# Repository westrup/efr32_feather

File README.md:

EFR32 Feather Board
===================

This is an Adafruit Feather compatible PCB with a Silicon Labs EFR32 MCU.
This MCU supports 2.4GHz radio such as BLE, Zigbee, Thread

Hardware components:
* MCU: EFR32 with 1024kB FLASH, 256kB RAM EFR32MG12P332F1024GM48
* USB Serial interface: CP2102N
* 3.3V LDO: AP2112K
* Charging: MCP73832

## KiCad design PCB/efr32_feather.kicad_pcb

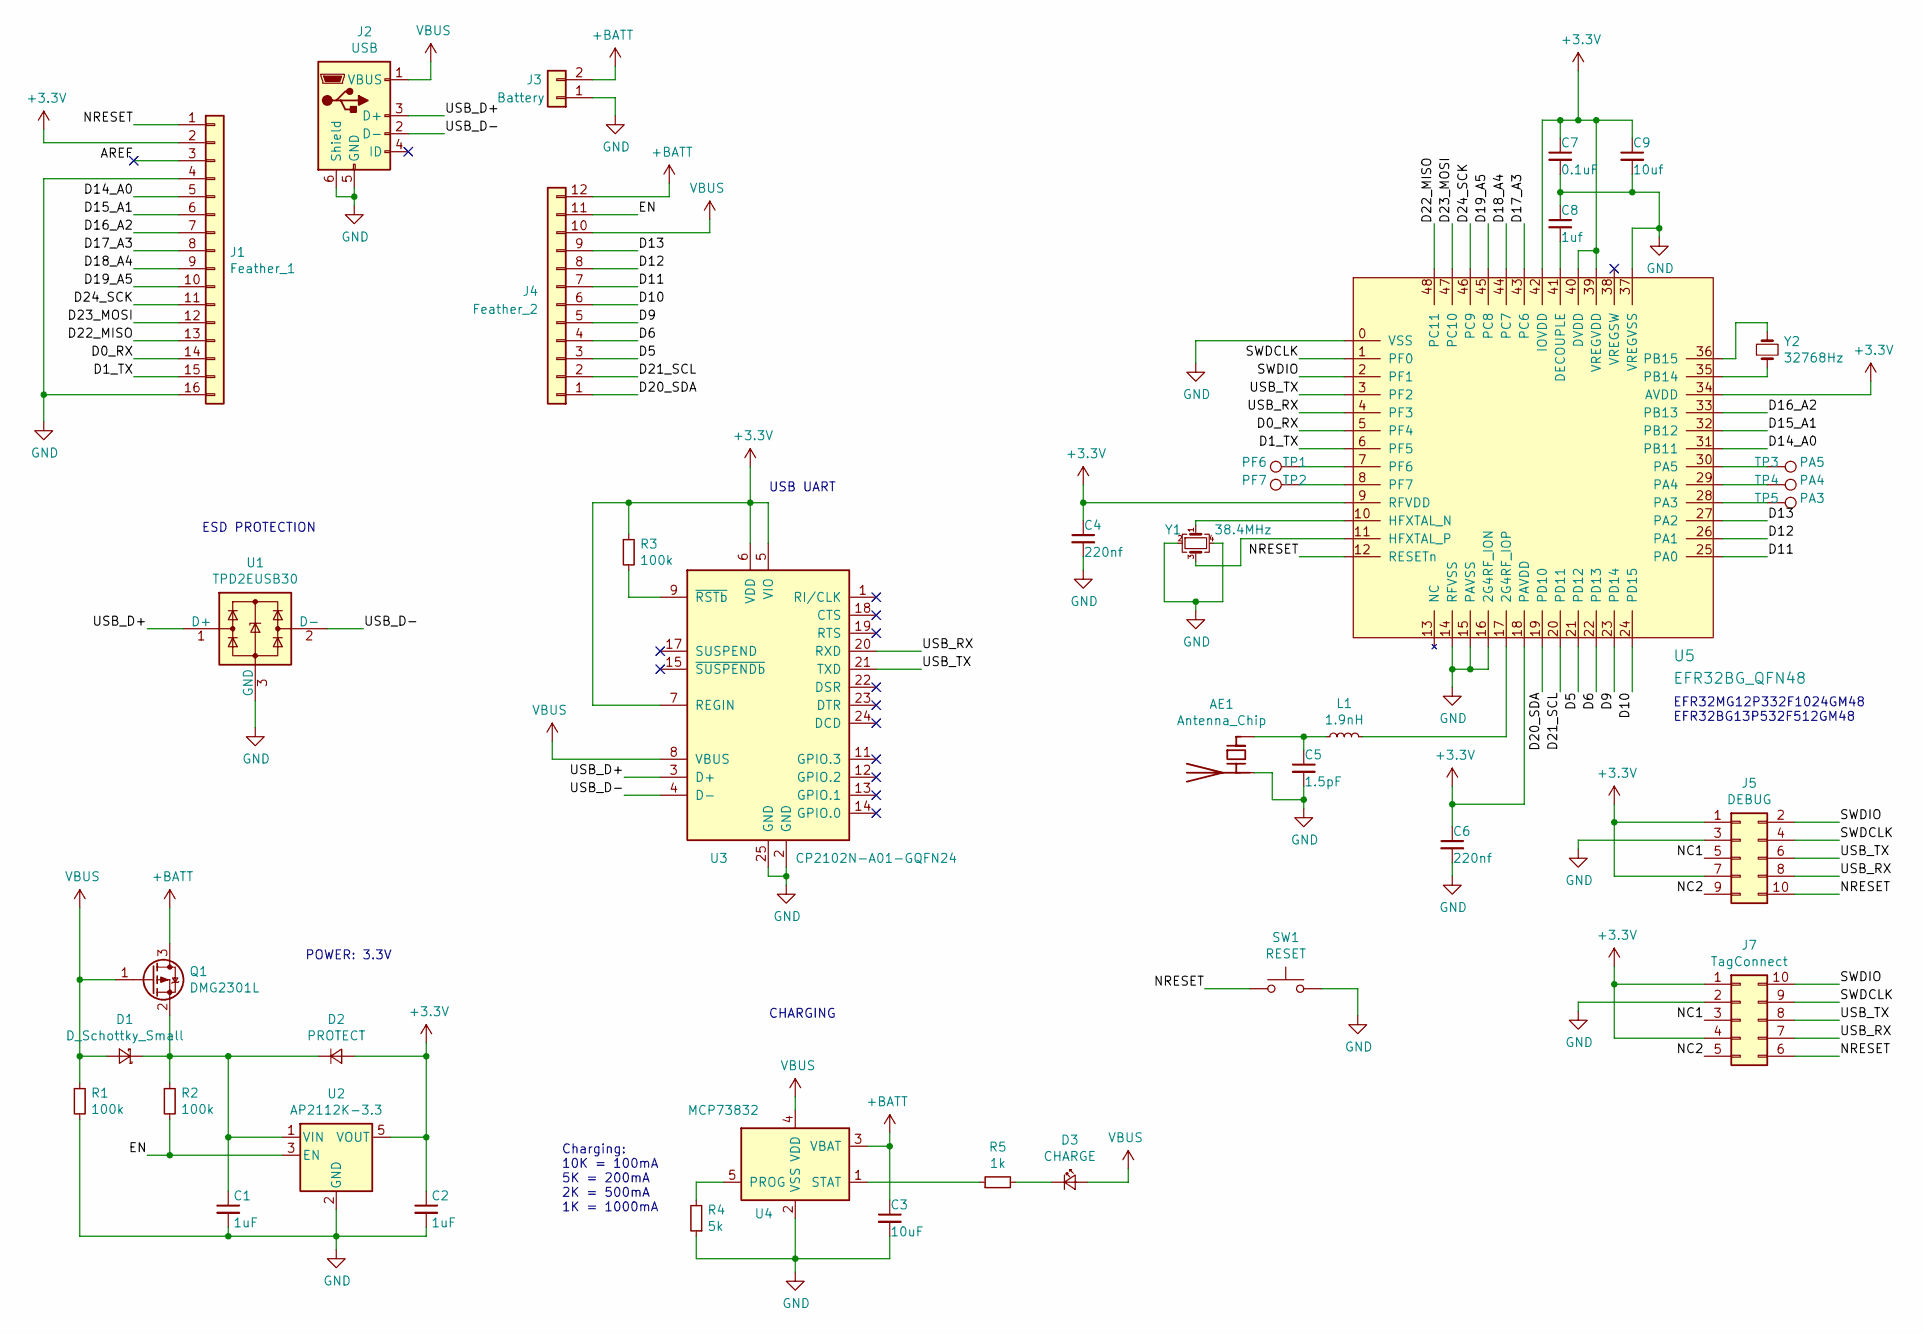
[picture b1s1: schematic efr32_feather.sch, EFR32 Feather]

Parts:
AE1: Antenna_Chip; Texas_SWRA117D_2.4GHz_Right
C1, C2: 1uF; C_0603_1608Metric
C3: 10uF; C_0603_1608Metric
C4, C6: 220nf; C_0603_1608Metric
C5: 1.5pF; C_0402_1005Metric
C7: 0.1uF; C_0603_1608Metric
C8: 1uf; C_0603_1608Metric
C9: 10uf; C_0603_1608Metric
D1: D_Schottky_Small; D_SOD-323
D2: PROTECT; D_SOD-323
D3: CHARGE; LED_0603_1608Metric
J1: Feather_1; PinHeader_1x16_P2.54mm_Vertical
J2: USB; USB_Micro-B_Molex-105017-0001
J3: Battery; JST_PH_S2B-PH-K_1x02_P2.00mm_Horizontal
J4: Feather_2; PinHeader_1x12_P2.54mm_Vertical
J5: DEBUG; PinHeader_2x05_P1.27mm_Vertical_SMD
J7: TagConnect; Tag-Connect_TC2050-IDC-NL_2x05_P1.27mm_Vertical
L1: 1.9nH; L_0402_1005Metric
Q1: DMG2301L; SOT-23
R1, R2, R3: 100k; R_0603_1608Metric
R4: 5k; R_0603_1608Metric
R5: 1k; R_0603_1608Metric
SW1: RESET; SW_SPST_B3U-1000P
TP1: PF6; TestPoint_Pad_D1.0mm
TP2: PF7; TestPoint_Pad_D1.0mm
TP3: PA5; TestPoint_Pad_D1.0mm
TP4: PA4; TestPoint_Pad_D1.0mm
TP5: PA3; TestPoint_Pad_D1.0mm
U1: TPD2EUSB30; Texas_DRT-3
U2: AP2112K-3.3; SOT-23-5
U3: CP2102N-A01-GQFN24; QFN-24-1EP_4x4mm_P0.5mm_EP2.6x2.6mm
U4: MCP73832; SOT-23-5
U5: EFR32BG_QFN48; QFN-48-1_PIN0_EP_7x7mm_P0.5mm_EP5.3x5.3mm
Y1: 38.4MHz; Crystal_SMD_3225-4Pin_3.2x2.5mm
Y2: 32768Hz; Crystal_SMD_3215-2Pin_3.2x1.5mm

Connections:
+3V3: C2.1, C4.1, C6.1, C7.1, C9.1, D2.2 (A), J1.2, J5.1, J5.7, J7.1, J7.4, R3.1, U2.5 (VOUT), U3.5 (VIO), U3.6 (VDD), U3.7 (REGIN), U5.9 (RFVDD), U5.18 (PAVDD), U5.34 (AVDD), U5.39 (VREGVDD), U5.40 (DVDD), U5.42 (IOVDD)
+BATT: C3.1, J3.2, J4.12, Q1.3 (D), U4.3 (VBAT)
/AREF: J1.3
/D0_RX: J1.14, U5.5 (PF4)
/D1_TX: J1.15, U5.6 (PF5)
/D5: J4.3, U5.21 (PD12)
/D6: J4.4, U5.22 (PD13)
/D9: J4.5, U5.23 (PD14)
/D10: J4.6, U5.24 (PD15)
/D11: J4.7, U5.25 (PA0)
/D12: J4.8, U5.26 (PA1)
/D13: J4.9, U5.27 (PA2)
/D14_A0: J1.5, U5.31 (PB11)
/D15_A1: J1.6, U5.32 (PB12)
/D16_A2: J1.7, U5.33 (PB13)
/D17_A3: J1.8, U5.43 (PC6)
/D18_A4: J1.9, U5.44 (PC7)
/D19_A5: J1.10, U5.45 (PC8)
/D20_SDA: J4.1, U5.19 (PD10)
/D21_SCL: J4.2, U5.20 (PD11)
/D22_MISO: J1.13, U5.48 (PC11)
/D23_MOSI: J1.12, U5.47 (PC10)
/D24_SCK: J1.11, U5.46 (PC9)
/EN: J4.11, R2.2, U2.3 (EN)
/NC1: J5.5, J7.3
/NC2: J5.9, J7.5
/NRESET: J1.1, J5.10, J7.6, SW1.1, U5.12 (RESETn)
/SWDCLK: J5.4, J7.9, U5.1 (PF0)
/SWDIO: J5.2, J7.10, U5.2 (PF1)
/USB_D+: J2.3 (D+), U1.1 (D+), U3.3 (D+)
/USB_D-: J2.2 (D-), U1.2 (D-), U3.4 (D-)
/USB_RX: J5.8, J7.7, U3.20 (RXD), U5.4 (PF3)
/USB_TX: J5.6, J7.8, U3.21 (TXD), U5.3 (PF2)
GND: AE1.2 (PCB_Trace), C1.2, C2.2, C3.2, C4.2, C5.2, C6.2, C7.2, C8.1, C9.2, J1.4, J1.16, J2.5 (GND), J2.6 (Shield), J3.1, J5.3, J7.2, R1.2, R4.1, SW1.2, U1.3 (GND), U2.2 (GND), U3.2 (GND), U3.25 (GND), U4.2 (VSS), U5.0 (VSS), U5.14 (RFVSS), U5.15 (PAVSS), U5.16 (2G4RF_ION), U5.37 (VREGVSS), Y1.2, Y1.4
unnamed: AE1.1 (FEED), C5.1, L1.1
unnamed: C1.1, D1.1 (K), D2.1 (K), Q1.2 (S), R2.1, U2.1 (VIN)
unnamed: C8.2, U5.41 (DECOUPLE)
unnamed: D3.1 (K), R5.2
unnamed: L1.2, U5.17 (2G4RF_IOP)
unnamed: R3.2, U3.9 (~RSTb)
unnamed: R4.2, U4.5 (PROG)
unnamed: R5.1, U4.1 (STAT)
unnamed: TP1.1, U5.7 (PF6)
unnamed: TP2.1, U5.8 (PF7)
unnamed: TP3.1, U5.30 (PA5)
unnamed: TP4.1, U5.29 (PA4)
unnamed: TP5.1, U5.28 (PA3)
unnamed: U5.10 (HFXTAL_N), Y1.1
unnamed: U5.11 (HFXTAL_P), Y1.3
unnamed: U5.35 (PB14), Y2.2
unnamed: U5.36 (PB15), Y2.1
VBUS: D1.2 (A), D3.2 (A), J2.1 (VBUS), J4.10, Q1.1 (G), R1.1, U3.8 (VBUS), U4.4 (VDD)

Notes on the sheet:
Charging: 10K = 100mA 5K = 200mA 2K = 500mA 1K = 1000mA
CHARGING
POWER: 3.3V
USB UART
ESD PROTECTION
EFR32MG12P332F1024GM48 EFR32BG13P532F512GM48

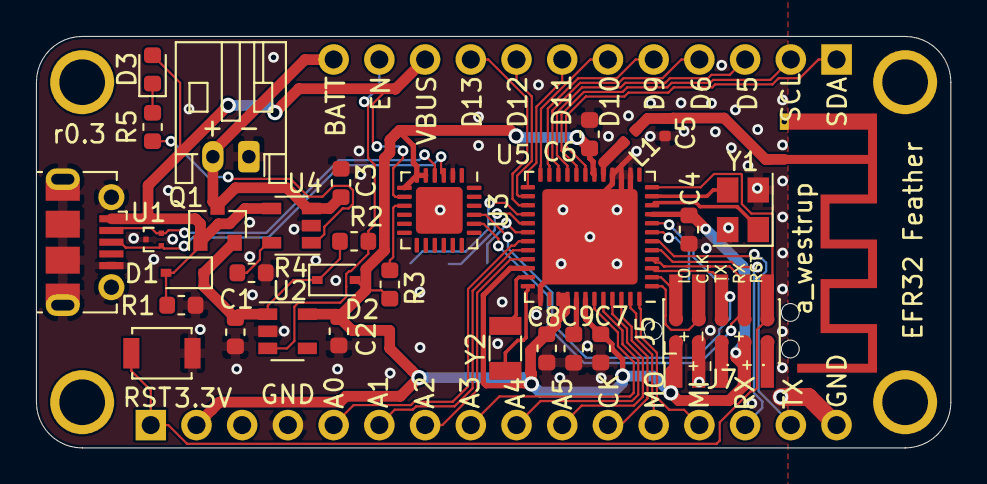
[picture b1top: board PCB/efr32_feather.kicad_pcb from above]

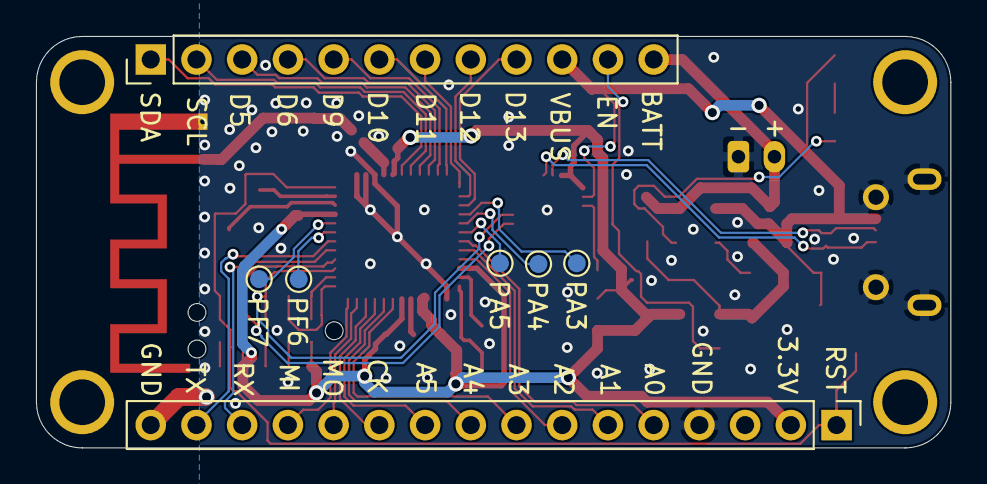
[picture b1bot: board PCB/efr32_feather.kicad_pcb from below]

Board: 2 copper layers, 50.8 x 22.9 mm, 40 parts (7 on the bottom side), 51 nets.

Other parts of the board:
PCB**: VAL**; PCB_FeatherWing

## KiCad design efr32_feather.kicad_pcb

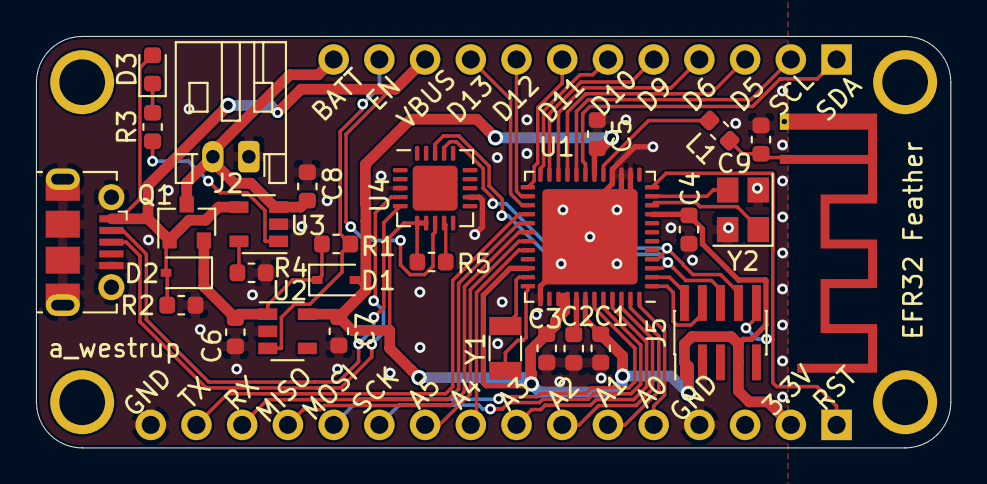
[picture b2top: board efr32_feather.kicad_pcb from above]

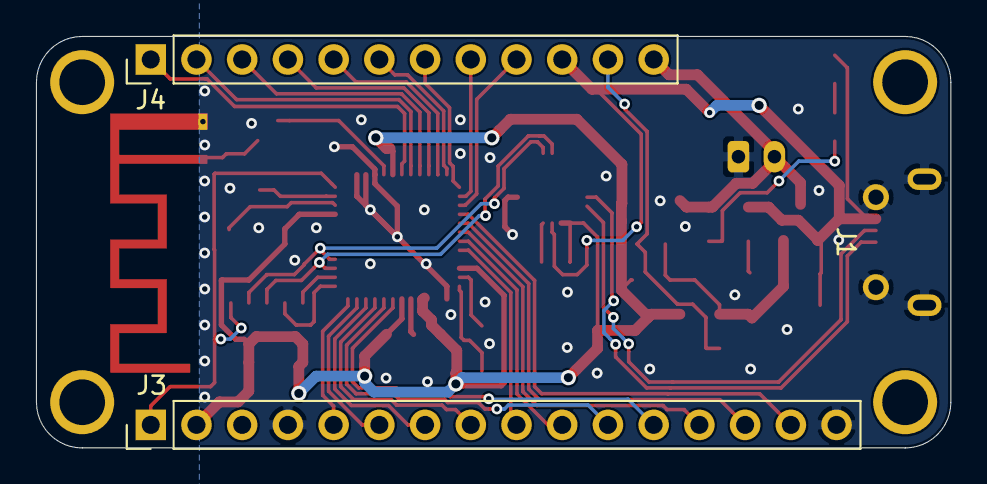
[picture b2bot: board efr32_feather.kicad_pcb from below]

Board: 2 copper layers, 50.8 x 22.9 mm, 32 parts (2 on the bottom side), 44 nets.

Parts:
AE1: Antenna_Chip; Texas_SWRA117D_2.4GHz_Right
C1: 0.1uF; C_0603_1608Metric
C2: 10uf; C_0603_1608Metric
C3: 1uf; C_0603_1608Metric
C4, C5: 220nf; C_0603_1608Metric
C6, C7: 1uF; C_0603_1608Metric
C8: 10uF; C_0603_1608Metric
C9: 1.5pF; C_0603_1608Metric
D1: PROTECT; D_SOD-323
D2: D_Schottky_Small; D_SOD-323
D3: CHARGE; LED_0603_1608Metric
J1: USB; USB_Micro-B_Molex-105017-0001
J2: Battery; JST_PH_S2B-PH-K_1x02_P2.00mm_Horizontal
J3: Feather_1; PinHeader_1x16_P2.54mm_Vertical
J4: Feather_2; PinHeader_1x12_P2.54mm_Vertical
J5: DEBUG; PinHeader_2x05_P1.00mm_Vertical_SMD
L1: 1.9nH; L_0603_1608Metric
PCB**: VAL**; PCB_FeatherWing
Q1: DMG2301L; SOT-23
R1, R2, R5: 100k; R_0603_1608Metric
R3: 1k; R_0603_1608Metric
R4: 5k; R_0603_1608Metric
U1: EFR32BG_QFN48; QFN-48-1_PIN0_EP_7x7mm_P0.5mm_EP5.3x5.3mm
U2: AP2112K-3.3; SOT-23-5
U3: MCP73831-2-OT; SOT-23-5
U4: CP2102N-A01-GQFN20; QFN-20-1EP_4x4mm_P0.5mm_EP2.5x2.5mm
Y1: 32768Hz; Crystal_SMD_3215-2Pin_3.2x1.5mm
Y2: 38.4MHz; Crystal_SMD_3225-4Pin_3.2x2.5mm

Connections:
+3V3: C1.1, C2.1, C4.1, C5.1, C7.1, D1.2, J3.2, J5.1, J5.7, R5.1, U1.9, U1.18, U1.34, U1.39, U1.40, U1.42, U2.5, U4.6, U4.7
+BATT: C8.1, J2.2, J4.12, Q1.3, U3.3
/D0_RX: J3.14, U1.29
/D1_TX: J3.15, U1.28
/D5: J4.3, U1.21
/D6: J4.4, U1.22
/D9: J4.5, U1.23
/D10: J4.6, U1.24
/D11: J4.7, U1.25
/D12: J4.8, U1.26
/D13: J4.9, U1.27
/D14_A0: J3.5, U1.48
/D15_A1: J3.6, U1.47
/D16_A2: J3.7, U1.46
/D17_A3: J3.8, U1.45
/D18_A4: J3.9, U1.32
/D19_A5: J3.10, U1.31
/D20_SDA: J4.1, U1.19
/D21_SCL: J4.2, U1.20
/D22_MISO: J3.13, U1.30
/D23_MOSI: J3.12, U1.43
/D24_SCK: J3.11, U1.44
/EN: J4.11, R1.2, U2.3
/NRESET: J3.1, J5.10, U1.12
/SWDCLK: J5.4, U1.1
/SWDIO: J5.2, U1.2
/USB_D+: J1.3, U4.4
/USB_D-: J1.2, U4.5
/USB_RX: J5.8, U1.4, U4.17
/USB_TX: J5.6, U1.3, U4.18
GND: AE1.2, C1.2, C2.2, C3.1, C4.2, C5.2, C6.2, C7.2, C8.2, C9.2, J1.5, J1.6, J2.1, J3.4, J3.16, J5.3, R2.2, R4.1, U1.0, U1.14, U1.15, U1.16, U1.37, U2.2, U3.2, U4.3, U4.12, Y2.2, Y2.4
unnamed: AE1.1, C9.1, L1.1
unnamed: C3.2, U1.41
unnamed: C6.1, D1.1, D2.1, Q1.2, R1.1, U2.1
unnamed: D3.1, R3.2
unnamed: L1.2, U1.17
unnamed: R3.1, U3.1
unnamed: R4.2, U3.5
unnamed: R5.2, U4.9
unnamed: U1.10, Y2.1
unnamed: U1.11, Y2.3
unnamed: U1.35, Y1.2
unnamed: U1.36, Y1.1
VBUS: D2.2, D3.2, J1.1, J4.10, Q1.1, R2.1, U3.4, U4.8

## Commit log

2019-09-16 EFR32 Feather
2019-09-16 Change debug connector
2019-09-16 Reversed pin header, better antenna traces, reset button
2019-09-16 Add ESD protection for USB
2019-09-16 Move HW files to PCB/ and add README file
2019-09-16 r0.2: moved antenna matching components, more silk screen
2019-09-16 Zephyr FW test code
2019-09-16 PIN names on silk screen
2019-09-16 Add links to README
